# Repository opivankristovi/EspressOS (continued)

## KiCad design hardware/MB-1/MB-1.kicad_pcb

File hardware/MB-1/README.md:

# MB-1: 6 analog in, 2 relays, 2 SSRs (rev A, design)

MB-1 is a 120 × 100 mm carrier board for an ESP32-WROOM-32E module. It is the hardware that the `eos-mb1` board profile in [web/js/boards.js](../../web/js/boards.js) describes. This document is the design: decisions, block diagram, pin map, terminal layout, circuits with values, the KiCad schematic and PCB, a BOM and layout rules.

**Status:** schematic done (generated, netlist-checked). PCB placed and routed (generated; DRC: no errors). Nothing has been ordered or built.

## Design decisions

| Topic | Choice | Why |
|---|---|---|
| Power | 5 V from USB-C only | One connector for power and programming; no supply on the board for 12/24 V. |
| Module | ESP32-WROOM-32E-N4 (PCB antenna) | GPIO 16 and 17 are relay outputs, so a WROVER module is ruled out: on WROVER those pins drive the PSRAM. Use the -32UE (external antenna) if the case sits in a metal cabinet. |
| Outputs | R1, R2: mechanical relays with NO and NC contacts. R3, R4: Omron G3MB-202P solid-state relays | Relays switch AC or DC and have a changeover contact. The SSRs switch AC silently and often (heaters, pumps). |
| Analog in | 6 × 0–10 V | The industrial standard; the same terminals also work as 12–24 V digital inputs. |
| Build | JLCPCB SMD assembly; through-hole parts (terminals, relays, SSRs, fuse holders) soldered by hand | |
| Enclosure | None: a bare board, 120 × 100 mm, five M3 holes | A 6-module DIN case (Camdenboss CNMB/6) has room for only 12 terminal poles per row at 3.5 mm and 9 at 5.08 mm; MB-1 needs 23 and 8. Mount it on standoffs inside a closed cabinet. |

> **Mains warning.** The relay contacts and the SSRs carry mains voltage on this PCB. Wiring and layout have to follow the creepage rules below. The board belongs in a closed enclosure, behind an upstream circuit breaker. Mains work must be done by someone qualified to do it.

## Block diagram

```mermaid
flowchart LR
  USB[USB-C<br/>5 V, data] --> PROT[PTC 1.5 A<br/>TVS 5 V<br/>ESD D+/D-]
  PROT -->|5V| LDO[AP7361C 3.3 V 1 A]
  PROT -->|5V| DRV
  PROT -->|D+/D-| UART[CH340C USB-serial<br/>auto-reset EN/IO0]
  LDO -->|3V3| ESP[ESP32-WROOM-32E]
  UART -->|TX/RX, EN, IO0| ESP
  AIN[AI1-AI6<br/>0-10 V] --> DIV[30k/10k divider<br/>clamp + 100 nF] --> ESP
  ESP -->|GPIO 16-19| DRV[4 × AO3400A low-side<br/>100k gate pull-down]
  DRV --> K12[K1, K2 relay SPDT<br/>COM / NO / NC]
  DRV --> K34[K3, K4 G3MB-202P SSR<br/>+ 2 A fuse]
  ESP <-->|GPIO 23,25,26,27,13,14| IO[IO1-IO6 3.3 V<br/>100 Ω + ESD]
  ESP <-->|GPIO 21/22| I2C[I2C terminals + Qwiic<br/>4.7k pull-ups]
  ESP <-->|GPIO 4| OW[1-Wire terminal<br/>4.7k pull-up]
```

## Pin map (must match the `eos-mb1` profile)

| GPIO | Terminal | Profile uses | Circuit | Notes |
|---|---|---|---|---|
| 36 (SENSOR_VP) | AI1 | ai, di | 0–10 V divider | input only, no internal pull |
| 39 (SENSOR_VN) | AI2 | ai, di | 0–10 V divider | input only |
| 34 | AI3 | ai, di | 0–10 V divider | input only |
| 35 | AI4 | ai, di | 0–10 V divider | input only |
| 32 | AI5 | ai, di | 0–10 V divider | internal pull-up must stay off (`pull: false`) |
| 33 | AI6 | ai, di | 0–10 V divider | same |
| 16 | R1 | do, active high | AO3400A → K1 relay coil | high-Z at reset, so a 100k pull-down keeps it off |
| 17 | R2 | do, active high | AO3400A → K2 relay coil | same |
| 18 | R3 | do, active high | AO3400A → K3 SSR input | same |
| 19 | R4 | do, active high | AO3400A → K4 SSR input | same |
| 23 | IO1 | di, do, pwm | 100 Ω + ESD | 3.3 V logic |
| 25 | IO2 | di, do, pwm | 100 Ω + ESD | |
| 26 | IO3 | di, do, pwm | 100 Ω + ESD | |
| 27 | IO4 | di, do, pwm | 100 Ω + ESD | |
| 13 | IO5 | di, do, pwm | 100 Ω + ESD | |
| 14 | IO6 | di | 100 Ω + ESD | input only in the profile: GPIO 14 outputs PWM during boot |
| 21 | SDA | I2C bus | 4.7k to 3V3, ESD | terminal and Qwiic connector |
| 22 | SCL | I2C bus | 4.7k to 3V3, ESD | |
| 4 | DQ | 1-Wire | 4.7k to 3V3, ESD | DS18B20 |
| 0 | — | BOOT button, auto-reset | 10k pull-up | strapping pin, not a terminal |
| EN | — | RESET button, auto-reset | 10k + 1 µF | |
| 1 / 3 | — | U0TXD / U0RXD → CH340C | | serial console and flashing |
| 2, 5, 12, 15 | — | not connected | | strapping pins; leave them open |
| 6–11 | — | module flash | | never route |

## Terminals

Mains is on the lower edge (5.08 mm pitch, rated 250 V). Safety extra-low voltage (SELV) is on the upper edge (3.5 mm pitch). USB-C and the RESET and BOOT buttons are on the left edge.

**Upper edge (SELV), left to right**

| Block | Positions |
|---|---|
| I2C (4) | 3V3 · SDA · SCL · GND |
| 1-Wire (3) | 3V3 · DQ · GND |
| Analog (8) | AI1 · AI2 · AI3 · AI4 · AI5 · AI6 · GND · GND |
| GPIO (8) | IO1 · IO2 · IO3 · IO4 · IO5 · IO6 · 3V3 · GND |
| Qwiic | Qwiic/STEMMA QT socket, at the right end |

**Lower edge (mains), left to right**

| Block | Positions | Rating on this board |
|---|---|---|
| R1 (3) | COM · NO · NC | 250 V AC / 30 V DC, 5 A (derated from the relay's 10 A for PCB and terminals) |
| R2 (3) | COM · NO · NC | same |
| R3, R4 (3) | SSR L in · R3 Load · R4 Load | 100–240 V AC, 0.1–2 A each, AC only; a 2 A fuse per SSR on board |

The two SSRs share one L input (J4 pin 1); each has its own fuse after that terminal. Wire both loads from the same phase.

The 3V3 terminal positions share a 200 mA PTC, so a shorted sensor cable cannot reset the ESP32.

## Circuits

### Power: USB-C 5 V
- J1: USB-C receptacle (USB 2.0, 16-pin). CC1 and CC2 each go to GND through their own 5.1 kΩ (R1, R2). Without those the C-to-C charger gives no power.
- F1: PTC, 1.5 A hold, on VBUS. D1: SMAJ5.0A TVS from VBUS to GND. C1 100 µF/16 V and C2 10 µF on the 5V rail.
- U2: AP7361C-33E (1 A, about 0.36 V dropout) from 5V to 3V3. Input C3 10 µF, output C4 22 µF + C5 100 nF. Do not use AMS1117: its 1.1 V dropout leaves no margin when USB VBUS sags.
- D2 + R3 1 kΩ: green power LED on 3V3.
- **Budget:** ESP32 Wi-Fi peaks at about 500 mA; each relay coil draws about 72 mA; each SSR input about 10–20 mA; LEDs about 10 mA. The total peak is about 0.75 A. Use a USB-C charger or a USB 3 port rated for at least 1 A. A USB 2 port (500 mA) may brown out when Wi-Fi transmits with both relays on.

### USB-serial and auto-reset
- U3: CH340C (internal oscillator), powered from **3V3**: VCC and V3 tied to 3V3, C6 100 nF. At 3.3 V its TXD cannot over-drive the ESP32's RX pin, which is not 5 V tolerant.
- U4: USBLC6-2SC6 on D+/D− at the connector.
- U3 TXD → ESP32 RXD0 (GPIO 3); U3 RXD → ESP32 TXD0 (GPIO 1).
- Auto-reset is the classic two-transistor circuit (Q1, Q2 MMBT3904, R4/R5 10 kΩ bases):
  - DTR → R4 → Q1 base. Q1 emitter goes to RTS and its collector to IO0.
  - RTS → R5 → Q2 base. Q2 emitter goes to DTR and its collector to EN.
- EN: R6 10 kΩ to 3V3 and C7 1 µF to GND (Espressif's RC delay); SW1 RESET to GND.
- IO0: R7 10 kΩ to 3V3; SW2 BOOT to GND. **Both buttons must be reachable through the front of the case:** the node firmware (mesh) uses BOOT at power-up to reopen its setup network.

### ESP32 module
- U1: ESP32-WROOM-32E-N4. 3V3 decoupling at the module: C8 22 µF + C9 100 nF + C10 100 nF.
- The antenna sits at a board edge with no copper on any layer under or next to it (see Espressif's keep-out drawing), as far as possible from the relays and the mains area.

### Outputs R1–R4 (×4, n = 1…4)
Each output is a low-side N-MOSFET with its gate held low, so the output is off while the ESP32 boots (GPIO 16–19 float at reset).

- GPIO → Rg(n) 100 Ω → gate Qn (AO3400A). Rpd(n) 100 kΩ from gate to GND.
- **R1, R2 (relays K1, K2, Omron G2RL-1 DC5):** coil between 5V and the drain. Flyback diode D(n) 1N4148W across the coil (cathode to 5V). Indicator LED + 1 kΩ from 5V to the drain.
- **R3, R4 (SSRs K3, K4, G3MB-202P):** input + to 5V, input − to the drain. Indicator LED + 1 kΩ from 5V to the drain. Load side: terminal "SSR L in" (shared) → fuse F3/F4 (2 A time-lag, TR5) → SSR terminal; the other SSR terminal goes to terminal "R3 Load" / "R4 Load". Pin order from the Omron data sheet: 1 and 2 load, 3 input +, 4 input −.
- G3MB-202P notes for the user:
  - It switches AC only; it never turns a DC load off.
  - Its built-in snubber passes a small leakage current, so a very small load such as an LED lamp under about 0.1 A can glow while the output is off. The profile note says 0.1–2 A for that reason.

### Analog inputs AI1–AI6 (×6)
Terminal → Rs 30 kΩ 1 % → node → ESP32 pin; node → Rb 10 kΩ 1 % to GND; node → C 100 nF to GND; node → BAT54S common pin. BAT54S pin 1 goes to GND and pin 2 to 3V3.

- Divider ratio 4: **10 V at the terminal = 2.5 V at the ADC**, inside the ESP32's useful 12 dB range. Full scale is reached at about 13 V.
- Input impedance is 40 kΩ, as 0–10 V sensors expect.
- Protected up to 30 V continuous: the clamp current is (30 − 3.6) / 30k ≈ 0.9 mA per input, well below what the ESP32 draws from 3V3.
- **As digital inputs** (`di`): high above about 10 V and low below about 3.3 V at the terminal. That works for 12 V and 24 V signals, but not for 5 V logic: use an IO terminal for that.
- **Scaling in the editor:** the AI block maps raw 0…4095 to min…max, and "Value at 3.3 V" is 13.2 V at the terminal. For a 0–10 V sensor that should read 0–100 %, set min 0 and max 132. The ESP32 ADC is not linear near both ends, so expect ±2–3 % without calibration (see Follow-ups).

### GPIO IO1–IO6 (×6)
- GPIO ← 100 Ω → terminal; ESD: U5 TPD4E05U06 (IO1–IO4), U6 TPD4E05U06 (IO5, IO6, SDA, SCL).
- These are 3.3 V logic pins, without isolation or level shifting. Inputs must stay within 0–3.3 V. Outputs give at most about 12 mA, enough for an LED, an external relay module input or a MOSFET module.

### I2C and 1-Wire
- SDA (GPIO 21) and SCL (GPIO 22): R 4.7 kΩ each to 3V3. Wired to the I2C terminal and J5 (JST SM04B-SRSS-TB, Qwiic pinout GND · 3V3 · SDA · SCL).
- DQ (GPIO 4): R 4.7 kΩ to 3V3. ESD: D (PESD3V3L1BA).
- F2: PTC 200 mA hold between 3V3 and the "3V3 out" net that feeds every 3V3 terminal position and J5.

## Schematic

[MB-1.kicad_sch](MB-1.kicad_sch) is the schematic (KiCad 8 format; it opens in KiCad 8, 9 and 10), and [MB-1.pdf](MB-1.pdf) is a print of it. Open [MB-1.kicad_pro](MB-1.kicad_pro) in KiCad.

**It is generated.** [gen_schematic.py](gen_schematic.py) holds every part, its value, footprint and part number, and the net on each pin. The script copies the symbols from KiCad's own libraries and draws the sheet:
- six blocks, matching the sections above;
- net labels at the pins and power symbols for GND, +5V and +3V3;
- a no-connect flag on every pin that isn't used.

To change the circuit, edit the script and generate again, rather than editing the sheet by hand:

```bash
python gen_schematic.py
kicad-cli sch erc MB-1.kicad_sch
kicad-cli sch export netlist --format kicadsexpr -o MB-1.net MB-1.kicad_sch
python check_netlist.py MB-1.net
kicad-cli sch export pdf -o MB-1.pdf MB-1.kicad_sch
```

[check_netlist.py](check_netlist.py) compares the netlist KiCad reads from the sheet with the nets in the script, pin by pin. A label that lands on the wrong pin would short or split a net without any ERC error. The current sheet gives 72 nets and 0 differences.

**ERC:** the electrical check has one expected error: "power output connected to power output" between U2 VO and U3 V3. The CH340C datasheet ties V3 to VCC when the chip runs at 3.3 V. Exclude it in KiCad's ERC dialog. On a KiCad install whose library tables were never set up, `kicad-cli` also lists "library not in the current configuration" warnings; those go away once KiCad has been started once.

**Parts that needed care:**
- *K3/K4 symbol:* KiCad has no Omron G3MB. The sheet uses the Sharp S202S02 symbol, which does the same job: input 3 (+) and 4 (−), output 1 and 2.
- *K3/K4 footprint:* `MB-1:Omron_G3MB-202P_SIP4` lives in the project library [MB-1.pretty](MB-1.pretty), drawn from Omron's G3MB data sheet (Cat. No. GC RLY8, page 3). It has four 1.0 mm holes on 1.8 mm pads, at 0, 7.62, 17.78 and 20.32 mm from pin 1 (top view). Pins 1 and 2 are the load and 3 (+) and 4 (−) the input. The body is 24.5 × 5.5 mm, with pin 4 1.69 mm from the body end. The [fp-lib-table](fp-lib-table) next to the project points KiCad to it. This is the standard G3MB-202P only: the "-4" variant has a different hole layout.
- *F3/F4:* these use TR5 fuse sockets (Littelfuse 560/460 series), so a blown fuse can be swapped.
- *K1/K2:* Omron G2RL-1 rather than the common HF3FF/SRD cube: on the cube footprint COM sits 6.3 mm from a coil pin, which leaves no room for 6 mm creepage after pads. The G2RL has its coil and contacts at opposite ends (KiCad footprint `Relay_THT:Relay_SPDT_Omron_G2RL-1`).

Reference designators on the sheet:

| Function | Refs |
|---|---|
| Power | J1, R1–R3, F1, D1, C1–C5, LED1, U2 |
| USB-serial, reset | U3, U4, Q1, Q2, R4–R7, C6, C7, SW1 (RESET), SW2 (BOOT) |
| ESP32 | U1, C8–C10 |
| Outputs (n = 1…4) | gate resistor R11–R14, gate pull-down R15–R18, MOSFET Q3–Q6, LED2–LED5 with R19–R22, relays K1/K2 with flyback D4/D5, SSRs K3/K4 with fuses F3/F4, terminals J2–J4 |
| Analog in (n = 1…6) | series R23–R28 (30k), to GND R29–R34 (10k), C11–C16, clamp D6–D11, terminal J6 |
| GPIO, buses | series R35–R40, ESD U5/U6 and D3, I2C pull-ups R8/R9, 1-Wire pull-up R10, PTC F2, terminals J7–J9, Qwiic J5 |

## PCB

[MB-1.kicad\_pcb](MB-1.kicad_pcb): two layers, 120 × 100 mm, all parts on top. Renders: [top](MB-1-top.png), [bottom](MB-1-bottom.png). Like the schematic it is generated, and then routed by a script:

```bash
"%LOCALAPPDATA%\Programs\KiCad\10.0\bin\python.exe" gen_pcb.py
"%LOCALAPPDATA%\Programs\KiCad\10.0\bin\python.exe" route.py
kicad-cli pcb drc MB-1.kicad_pcb
```

* **[gen\_pcb.py](gen_pcb.py)** reads the parts and nets from `gen_schematic.py`, places every footprint, and writes the outline, mounting holes, silkscreen labels, ground pours and design rules. Footprints keep their schematic links, so *Update PCB from Schematic* in KiCad still works. Ground pads that tracks would fence in (U4, U5, U6, the AI filter caps, each output driver's MOSFET source and gate pull-down) get a locked via before routing. Strips 0.5 mm wide along the board edge keep tracks off it. `gen_pcb.py --silk` copies the part fields (values, MPN, LCSC) from `gen_schematic.py` and redoes the silkscreen on the routed board, without touching copper.
* **[route.py](route.py)** exports the board to Freerouting, routes it (about 15 minutes), reads the result back and cleans up after it: it removes loose vias and dead-end stubs, fills the pours, adds ground stitching vias on a 4 mm grid (0.5 mm from any other hole), joins every piece of ground pour that is cut off from the main ground with a via, and widens the few tracks Freerouting necks below 0.13 mm. Freerouting's router is deterministic and can stall with a net open; route.py then retries with a slightly larger clearance margin. It needs the Freerouting 2.5 jar (from its GitHub releases) and Java 25; the native `freerouting-cli` 2.5.0 build crashes and then hangs. Freerouting's log goes to `MB-1.route.log`.

**Layout.** SELV parts fill the top 65 mm: terminals along the top edge, the ESP32 at the right edge with its antenna past the copper, USB-C and the power and USB-serial parts on the left, the four output drivers in a row above the keep-out. A 6 mm keep-out band across the board (y 65.6–71.6 mm) carries no copper on either layer. Below it are only mains parts: K1/K2 above J2/J3 on the left, K3/K4 with F3/F4 and J4 on the right. Relay coils and SSR inputs are the only things that bridge the band, through the parts themselves.

**Rules** ([MB-1.kicad\_dru](MB-1.kicad_dru) and the net classes in the project):

|Net class / rule|Clearance|Track|
|-|-|-|
|Default|0.2 mm|0.25 mm|
|Power (GND, +5V, +3V3, VBUS, 3V3 out, relay drivers)|0.2 mm|0.6 mm|
|Mains (relay contacts, SSR load side)|2.0 mm|2.0 mm|
|Mains to anything not mains|6.0 mm| |
|Mains to a mounting hole|6.0 mm| |

Mains tracks are 2 mm wide on both layers. That carries 5 A with about 20 °C rise on 1 oz copper; order 2 oz copper, or tin the mains tracks, if the relays will switch close to 5 A continuously.

**DRC:** no errors and no unconnected items. The warnings left are "footprint library not in the current configuration" (as with ERC, until KiCad has been started once) and 8 places in the driver row where reference text touches a pad; the fab clips silkscreen off pads.

**Open before ordering:**

* Milled slots between relay coil and contact pins, and between SSR input and load pins (the layout rules ask for them; the 6 mm clearance already holds without them).
* Gerbers, and a check of the part rotations in JLCPCB's placement preview (see *Ordering at JLCPCB*).
* A look at the board in KiCad's 3D viewer and a printout at 1:1 to check the terminal and relay footprints against real parts.

## 3D model for an enclosure

[3d/MB-1.stl](3d/MB-1.stl) is the assembled board as one mesh (binary STL, mm), for designing an enclosure in Fusion, TinkerCAD or any CAD that imports STL. [make\_3d.py](make_3d.py) makes it from the routed board:

```bash
"%LOCALAPPDATA%\Programs\KiCad\10.0\bin\python.exe" make_3d.py
```

KiCad's library has no 3D model for the USB-C socket, the G2RL relays, the 1812 PTC or the project's own G3MB footprint. For those the script adds a solid block: the body outline from the footprint's fabrication drawing, the height from the data sheet (maximum).

**Coordinates.** The origin is the board's lower-left corner, with low voltage at the top and mains at the bottom, as in the renders. X runs along the 120 mm edge and Y along the 100 mm edge. Z runs up from the bottom of the board, so the top surface is at z = 1.6.

**What the enclosure has to clear** (from the model):

|Item|Where (mm)|Height (z, mm)|
|-|-|-|
|Board|0–120 × 0–100, 1.6 thick, 2 mm corner radius|0–1.6|
|Mounting holes, M3 (3.2 mm)|(3.5, 3.5), (116.5, 3.5), (62, 3.5), (3.5, 96.5), (116.5, 96.5)| |
|Pins and solder below the board|whole board|down to −2.9: standoffs of 5 mm or more|
|SSRs K3/K4 (tallest)|x 64.2–69.8 and 72.2–77.8, y 15.5–40.1|up to 22.1|
|Relays K1/K2|x 9.5–22.0 and 28.4–41.1, y 13.4–42.3|up to 17.3|
|Mains terminals J2, J3, J4 (screws on top, wires in from the bottom edge)|y 0.9–10.7; x 8.7–43.7 and 80.7–94.9|up to 15.4|
|Low-voltage terminals J6–J9 (screws on top, wires in from the top edge)|y 85.8–99.0, x 10.1–99.6|up to 10.8|
|Qwiic socket J5 (opening to the top edge)|x 98–104, y 93.5–98.5|up to 4.6|
|USB-C J1 (opening to the left edge)|mouth at x 0.7, y 65.5–74.5|1.6–4.9|
|RESET / BOOT buttons (pressed from above)|x 1.8–8.2, y 44.9–58.6|up to 3.1|
|Fuse sockets F3/F4|x 99–108, y 9–29|socket 7.2; the TR5 fuse sits on top: measure with the fuse fitted|
|ESP32 antenna|x 94.5–119.5, y 55–73 (module), antenna at the right edge|keep metal away from the right edge|

The enclosure has to keep fingers off the mains side. All mains copper (relay contacts, SSR load pins, fuses, terminals J2–J4) lies below the copper-free band at y 28.4–34.4; the relay and SSR bodies straddle that band.

## BOM (one board)

Every part has an LCSC number (the `LCSC` field in the schematic and PCB, set in the `ORDER` table of [gen\_schematic.py](gen_schematic.py)). They were looked up in JLCPCB's parts catalogue on 12 November 2026; stock changes, so check the numbers again when ordering. **Basic** parts carry no setup fee at JLCPCB; every other (extended) SMD part costs $3 per order. MB-1 has 15 extended SMD parts.

**SMD, placed by JLCPCB**

| Ref | Qty | Part | MPN | LCSC | Type |
|---|---|---|---|---|---|
| U1 | 1 | ESP32 module, 4 MB | Espressif ESP32-WROOM-32E-N4 | C701341 | extended |
| U2 | 1 | LDO 3.3 V 1 A, SOT-223 | Diodes AP7361C-33E-13 | C500795 | extended (low stock, about 2,500) |
| U3 | 1 | USB-serial, SOP-16 | WCH CH340C | C84681 | extended |
| U4 | 1 | USB ESD, SOT-23-6 | ST USBLC6-2SC6 | C7519 | extended |
| U5, U6 | 2 | 4-ch ESD, USON-10 | TI TPD4E05U06DQAR | C138714 | extended |
| Q1, Q2 | 2 | NPN, SOT-23 | MMBT3904 | C20526 | basic |
| Q3–Q6 | 4 | N-MOSFET logic level, SOT-23 | AOS AO3400A | C20917 | basic |
| D1 | 1 | TVS 5 V, SMA | Littelfuse SMAJ5.0A | C83329 | extended |
| D3 | 1 | ESD diode for DQ, SOD-323 | Nexperia PESD3V3L1BA,115 | C51450 | extended |
| D4, D5 | 2 | Flyback diode, SOD-123 | 1N4148W | C81598 | basic |
| D6–D11 | 6 | Schottky pair, SOT-23 | Nexperia BAT54S,215 | C47546 | extended |
| F1 | 1 | PTC 1.5 A hold, 1812 | Bourns MF-MSMF150-2 | C89648 | extended |
| F2 | 1 | PTC 0.2 A hold, 1206 | Bourns MF-NSMF020-2 | C185112 | extended |
| J1 | 1 | USB-C 16-pin receptacle | HRO TYPE-C-31-M-12 | C165948 | extended |
| J5 | 1 | Qwiic socket | JST SM04B-SRSS-TB(LF)(SN) | C160404 | extended |
| SW1, SW2 | 2 | Tact switch 5.2 mm | E-Switch TL3342F450QG | C2886897 | extended (about 600 in stock) |
| LED1 | 1 | LED green 0603 | KENTO KT-0603G | C12624 | extended |
| LED2–LED5 | 4 | LED red 0603 | KENTO KT-0603R | C2286 | basic |
| C1 | 1 | 100 µF 16 V electrolytic, 6.3 × 5.4 mm | KNSCHA RVT100UF16V67RV0016 | C2887276 | extended |
| C2, C3 | 2 | 10 µF 25 V X5R 0805 | Samsung CL21A106KAYNNNE | C15850 | basic |
| C4, C8 | 2 | 22 µF 25 V X5R 0805 | Samsung CL21A226MAQNNNE | C45783 | basic |
| C5, C6, C9–C16 | 10 | 100 nF 50 V X7R 0603 | Yageo CC0603KRX7R9BB104 | C14663 | basic |
| C7 | 1 | 1 µF 50 V X5R 0603 | Samsung CL10A105KB8NNNC | C15849 | basic |
| R1, R2 | 2 | 5.1 kΩ 1 % 0603 | Uniroyal 0603WAF5101T5E | C23186 | basic |
| R3, R19–R22 | 5 | 1 kΩ 1 % 0603 | Uniroyal 0603WAF1001T5E | C21190 | basic |
| R4–R7, R29–R34 | 10 | 10 kΩ 1 % 0603 | Uniroyal 0603WAF1002T5E | C25804 | basic |
| R8–R10 | 3 | 4.7 kΩ 1 % 0603 | Uniroyal 0603WAF4701T5E | C23162 | basic |
| R11–R14, R35–R40 | 10 | 100 Ω 1 % 0603 | Uniroyal 0603WAF1000T5E | C22775 | basic |
| R15–R18 | 4 | 100 kΩ 1 % 0603 | Uniroyal 0603WAF1003T5E | C25803 | basic |
| R23–R28 | 6 | 30 kΩ 1 % 0603 | Uniroyal 0603WAF3002T5E | C22984 | basic |

Notes:

* *C1* is 5.4 mm tall rather than 7.7 mm: no 100 µF part in the 6.3 × 7.7 mm size was in stock. Its pads are 0.1 mm further in than the board's 6.3 × 7.7 mm land pattern, which takes it without change.
* *F2* is the 1206 version (MF-**N**SMF020-2). The MSMF series that the first BOM named is 1812 and would not fit the footprint.

**Through-hole, soldered by hand** (order from LCSC or any distributor)

| Ref | Qty | Part | MPN | LCSC | Stock at LCSC |
|---|---|---|---|---|---|
| K1, K2 | 2 | Relay SPDT 5 V 12 A | Omron G2RL-1 DC5 | C1524672 | about 1,100 |
| K3, K4 | 2 | SSR 2 A AC, zero-cross, SIP-4 | Omron G3MB-202P DC5 | C19591980 | **none**: buy elsewhere (Mouser, DigiKey, Farnell) |
| F3, F4 | 2 | TR5 fuse socket | Littelfuse 56000001009 | C142909 | yes |
| (in F3, F4) | 2 | Fuse 2 A time-lag, TR5 | Littelfuse 37212000001 | C142854 | about 1,400 |
| J2–J4 | 3 | Screw terminal 3-pos 5.08 mm | Phoenix MKDS 1,5/ 3-5,08 (1715734) | C480520 | about 1,100 |
| J6, J7 | 2 | Screw terminal 8-pos 3.5 mm | Phoenix PT 1,5/ 8-3,5-H (1984675) | C5484501 | **none**: buy elsewhere |
| J8 | 1 | Screw terminal 3-pos 3.5 mm | Phoenix PT 1,5/ 3-3,5-H (1984620) | C3816291 | about 500 |
| J9 | 1 | Screw terminal 4-pos 3.5 mm | Phoenix PT 1,5/ 4-3,5-H (1984633) | C5144867 | about 200 |
| — | 5 | M3 standoffs and screws | any | | |

### Ordering at JLCPCB

```bash
"%LOCALAPPDATA%\Programs\KiCad\10.0\bin\python.exe" jlc.py
"%LOCALAPPDATA%\Programs\KiCad\10.0\bin\python.exe" jlc_check.py
```

[jlc.py](jlc.py) writes the three files JLCPCB asks for, from the routed board:

* [jlcpcb/MB-1-gerbers.zip](jlcpcb/MB-1-gerbers.zip): copper, mask, paste and silkscreen on both sides, the outline, and plated and non-plated drill files (Protel file names, silkscreen clipped at the mask openings, drill in mm), as JLCPCB's KiCad guide asks. Two-layer board, 120 × 100 mm.
* [jlcpcb/MB-1-bom.csv](jlcpcb/MB-1-bom.csv): the 89 SMD parts in 32 lines, with their LCSC numbers.
* [jlcpcb/MB-1-cpl.csv](jlcpcb/MB-1-cpl.csv): position (mm from the board's lower-left corner) and rotation of each SMD part.

JLCPCB places its own library footprint for each LCSC part, and for some packages its zero rotation or origin differs from KiCad's. The `JLC_FIX` table in jlc.py corrects those: +180° for the SOT-23 parts (Q1–Q6, D6–D11) and the AP7361C, +270° for the CH340C, USBLC6 and TPD4E05U06, and +270° plus a 3.68 mm offset for the ESP32. The USB-C socket keeps its rotation but gets a 1.57 mm offset. [jlc_check.py](jlc_check.py) verifies the result the way JLCPCB's placement preview does: it fetches each part's footprint from EasyEDA (JLCPCB's library) and fits its numbered pads onto the KiCad pads. It also compares both libraries' pin names per pad, which caught the red LEDs (C2286): their pad 1 is the anode, KiCad's is the cathode, so a plain pad-number match would have turned them round. All 89 parts check out: right rotation, centred within 0.1 mm, and the same pinout and polarity. The largest pad difference left is 0.4 mm on the CH340C, where JLCPCB's SOIC land pattern is wider.

Still worth one look in JLCPCB's own placement preview when ordering (it needs a JLCPCB account): the check uses the same library data, but the preview is what the factory goes by.

## Layout rules

- **Mains area** (K1–K4 load side, F3/F4, J2–J4) on the lower part of the board.
  - At least **6 mm creepage and clearance** between any mains net and any SELV net.
  - Milled slots under the relays and SSRs between coil/input pins and contact/load pins.
  - At least 3 mm between different mains channels.
  - Load traces at least 3 mm wide on 1 oz copper, or 2 mm on 2 oz, both layers, for 5 A.
  - No ground pour inside the mains area.
- **SELV area:** one solid GND plane. The ESP32, the LDO and the CH340C sit away from the relay coil current loops.
- Antenna keep-out at the right board edge, away from the relays; keep the cabinet wall near that edge non-metallic.
- Each analog divider sits close to its ESP32 pin, with the 100 nF capacitor right at the pin.
- Silkscreen: terminal labels exactly as the profile names them (AI1…AI6, R1…R4, IO1…IO6), plus "MB-1 rev A".

## Bring-up checklist

1. With no module fitted: power on USB-C and check 5V and 3V3. Measure that DRV1–4 are high (outputs off).
2. Fit the module and flash `pio run -t upload && pio run -t uploadfs` over USB with no button presses. That tests the auto-reset circuit.
3. In the editor, choose Settings → Board → **MB-1** and let it restart. Deploy a program with one DO per output and check that each relay and SSR clicks or switches on its own channel. Power-cycle and confirm that nothing switches during boot.
4. Feed 0, 5 and 10 V to each AI and check the readings (expect raw about 0, 1550 and 3100).
5. Scan I2C with a sensor on the Qwiic socket, and read a DS18B20 on the 1-Wire terminal.

## Follow-ups (not part of rev A)

- **Analog in volts.** Let the firmware read the ADC with `analogReadMilliVolts` (Espressif's calibration), and give a profile terminal an optional scale (here ×4). The AI block would then show terminal volts, so users wouldn't need the "max 132" rule above. That needs a profile schema change in both validators.
- **Power option.** A 24 V version (buck converter to 5 V) for cabinets where USB power is unusual.

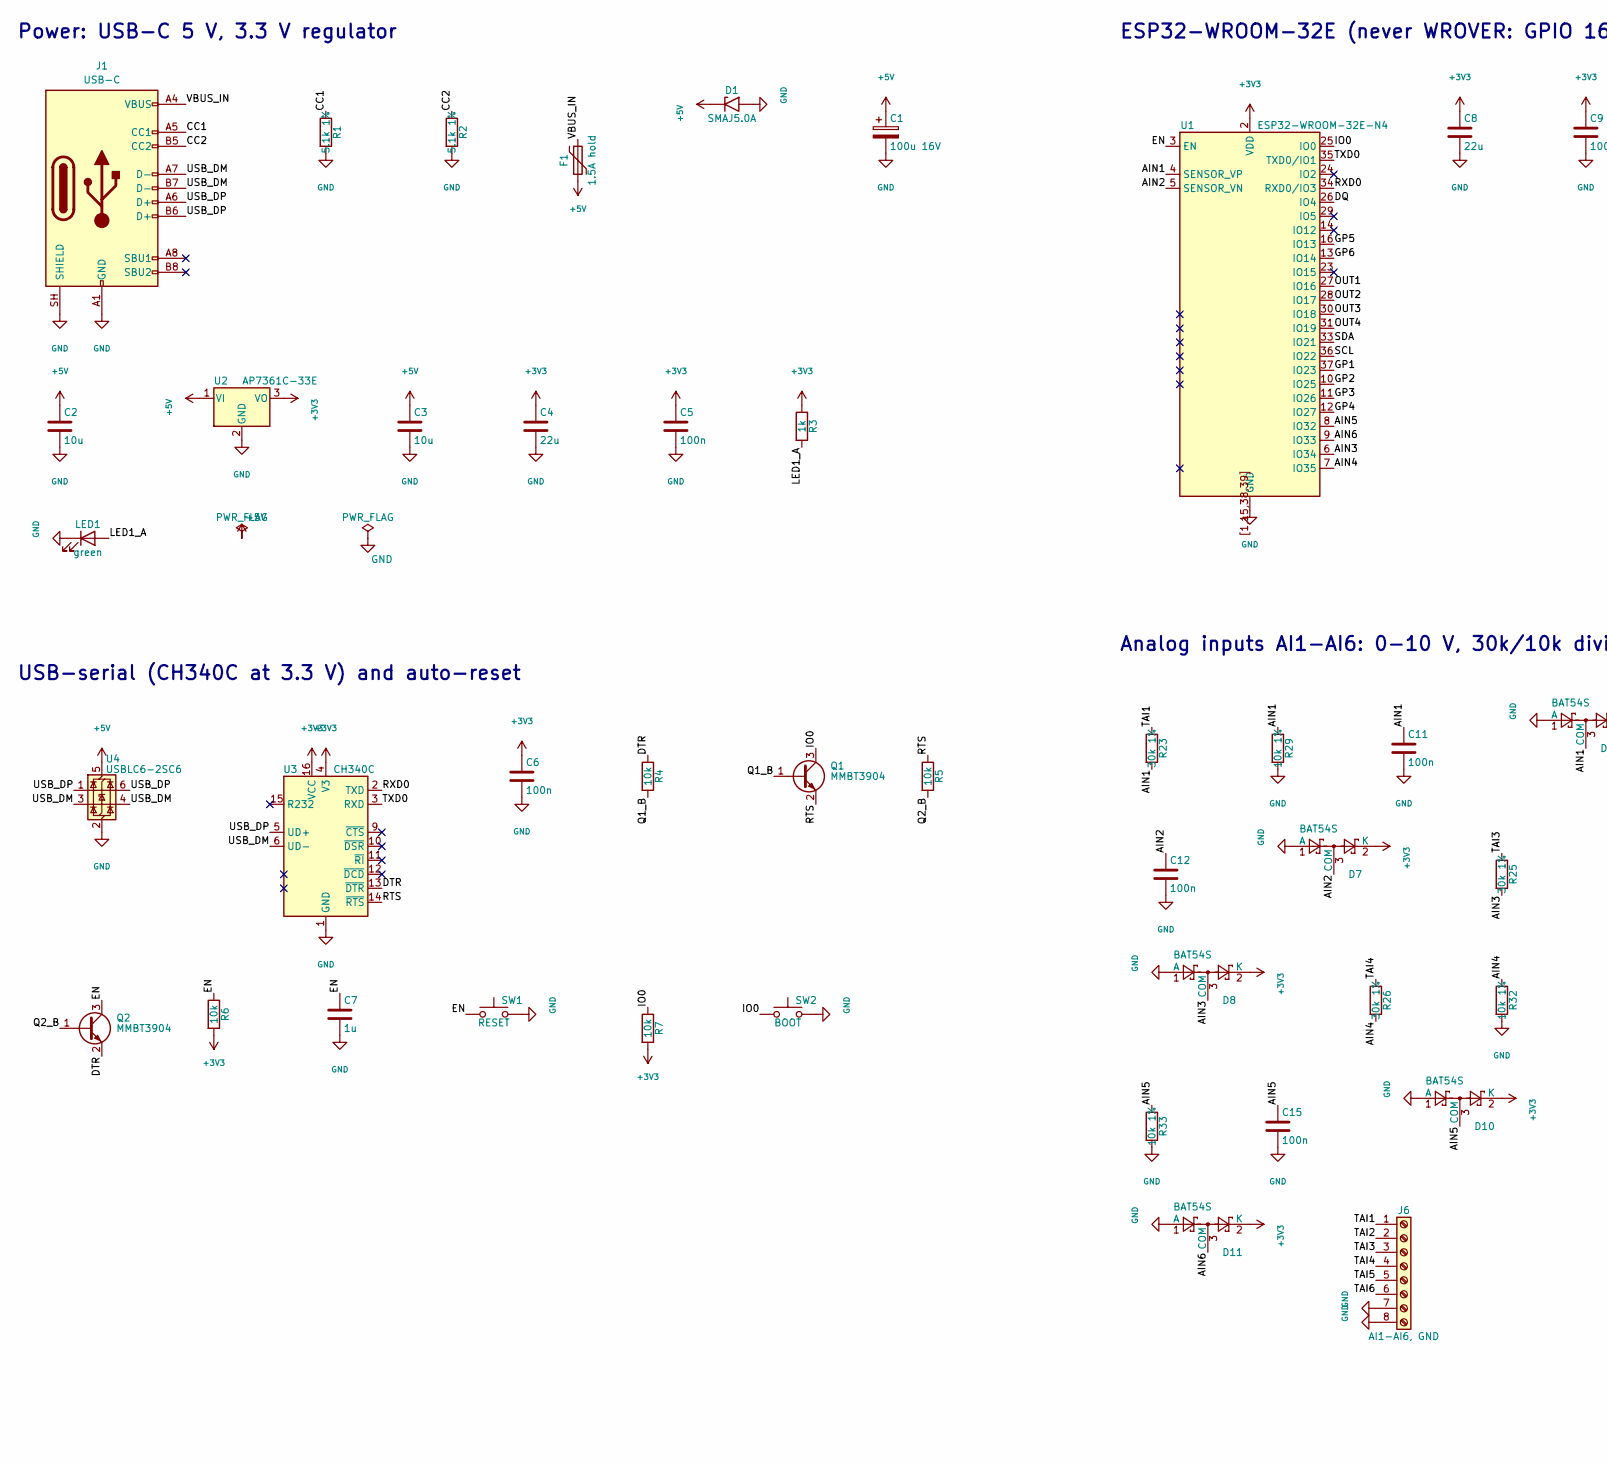
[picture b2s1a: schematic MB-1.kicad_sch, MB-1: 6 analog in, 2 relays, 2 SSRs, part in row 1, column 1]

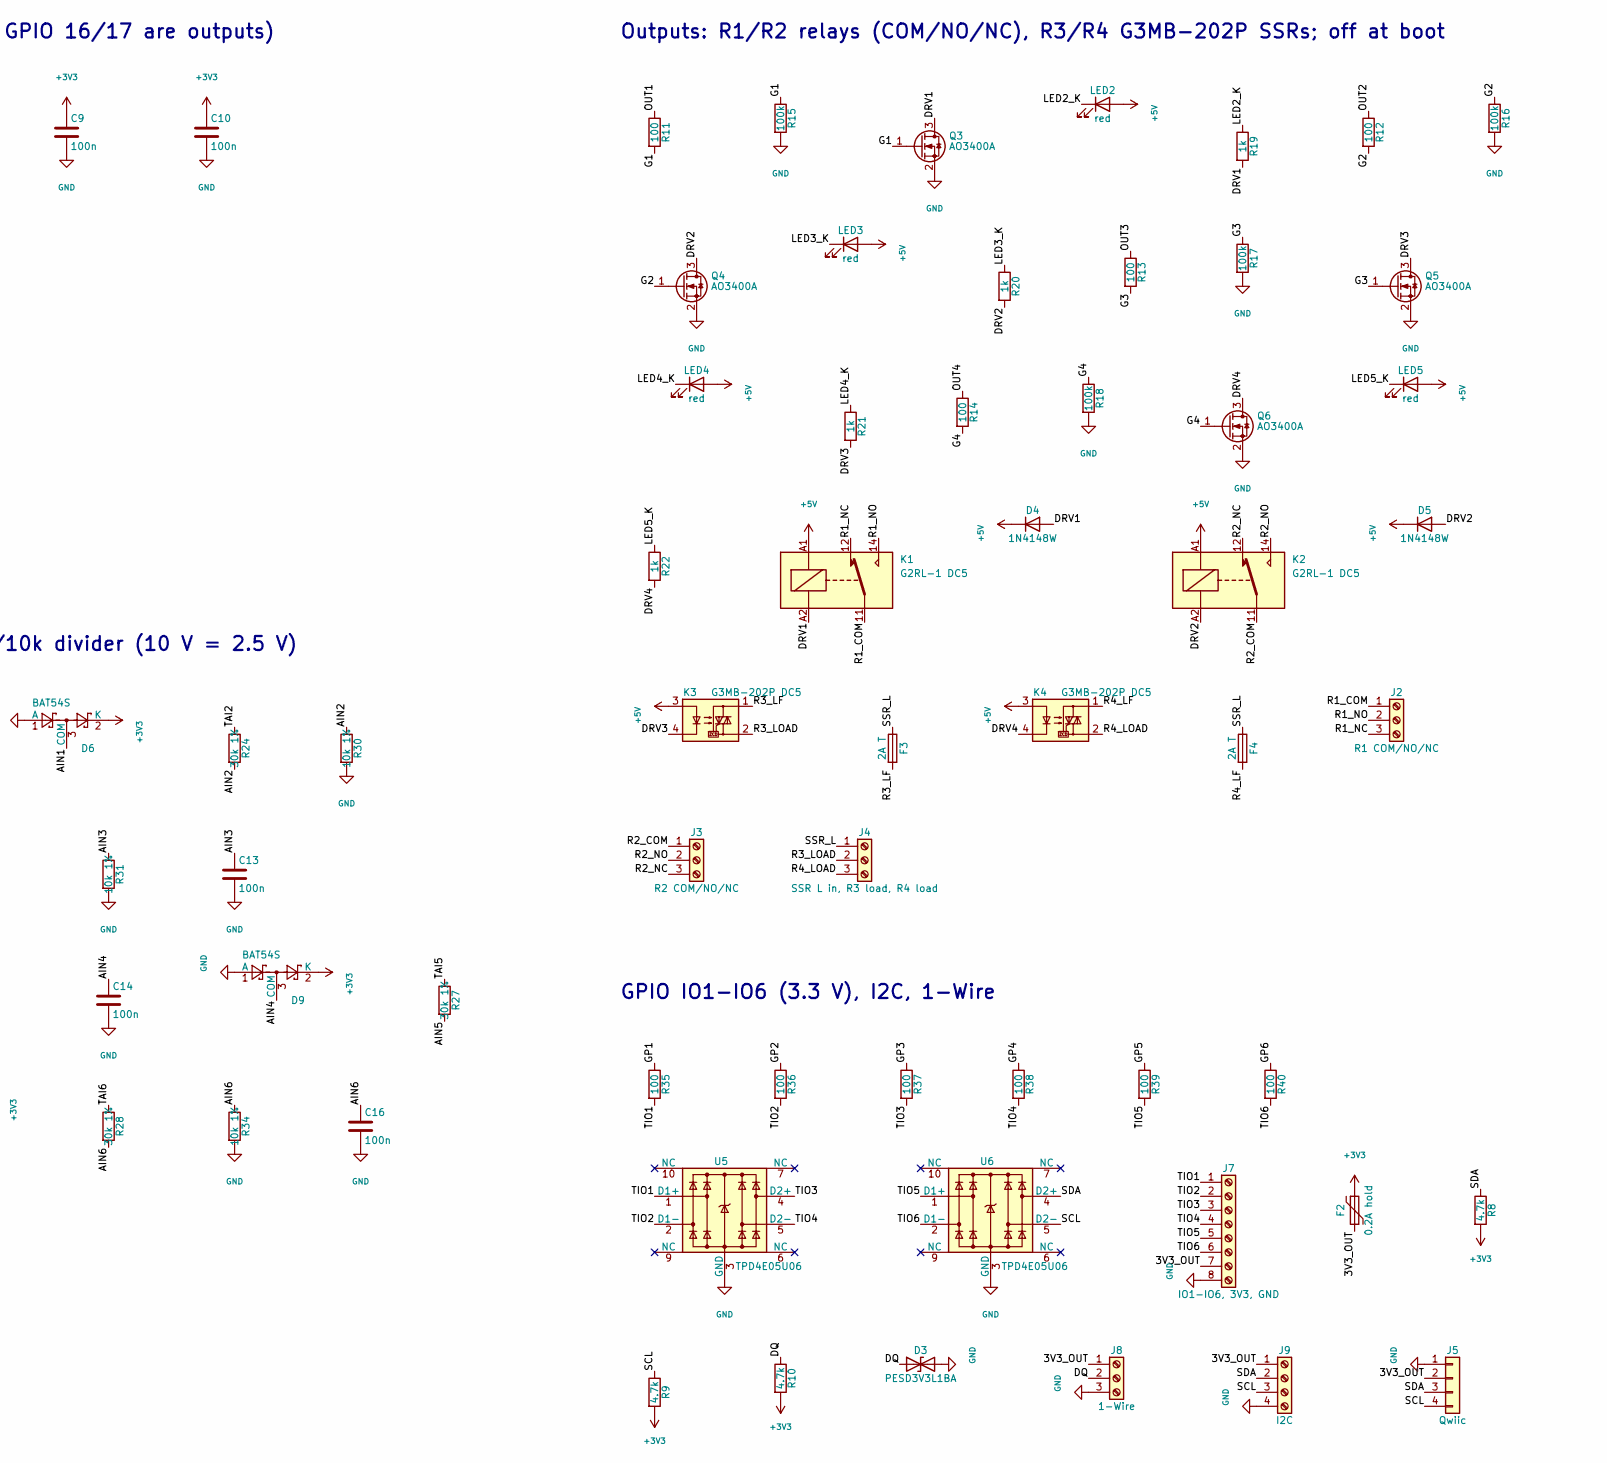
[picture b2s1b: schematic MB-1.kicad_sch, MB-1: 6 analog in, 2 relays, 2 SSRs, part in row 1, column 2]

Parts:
C1: 100u 16V; CP_Elec_6.3x7.7; MPN KNSCHA RVT100UF16V67RV0016; LCSC C2887276
C2, C3: 10u; C_0805_2012Metric; MPN Samsung CL21A106KAYNNNE; LCSC C15850
C4, C8: 22u; C_0805_2012Metric; MPN Samsung CL21A226MAQNNNE; LCSC C45783
C5, C6, C9, C10, C11, C12, C13, C14, C15, C16: 100n; C_0603_1608Metric; MPN Yageo CC0603KRX7R9BB104; LCSC C14663
C7: 1u; C_0603_1608Metric; MPN Samsung CL10A105KB8NNNC; LCSC C15849
D1: SMAJ5.0A; D_SMA; MPN Littelfuse SMAJ5.0A; LCSC C83329
D3: PESD3V3L1BA; D_SOD-323; MPN Nexperia PESD3V3L1BA,115; LCSC C51450
D4, D5: 1N4148W; D_SOD-123; MPN 1N4148W; LCSC C81598
D6, D7, D8, D9, D10, D11: BAT54S; SOT-23; MPN Nexperia BAT54S,215; LCSC C47546
F1: 1.5A hold; Fuse_1812_4532Metric; MPN Bourns MF-MSMF150-2; LCSC C89648
F2: 0.2A hold; Fuse_1206_3216Metric; MPN Bourns MF-NSMF020-2; LCSC C185112
F3, F4: 2A T; Fuseholder_TR5_Littelfuse_No560_No460; MPN Littelfuse 56000001009; LCSC C142909
J1: USB-C; USB_C_Receptacle_HRO_TYPE-C-31-M-12; MPN HRO TYPE-C-31-M-12; LCSC C165948
J2: R1 COM/NO/NC; TerminalBlock_Phoenix_MKDS-1,5-3-5.08_1x03_P5.08mm_Horizont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; MPN Phoenix MKDS 1,5/ 3-5,08 (1715734); LCSC C480520
J3: R2 COM/NO/NC; TerminalBlock_Phoenix_MKDS-1,5-3-5.08_1x03_P5.08mm_Horizont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; MPN Phoenix MKDS 1,5/ 3-5,08 (1715734); LCSC C480520
J4: SSR L in, R3 load, R4 load; TerminalBlock_Phoenix_MKDS-1,5-3-5.08_1x03_P5.08mm_Horizont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; MPN Phoenix MKDS 1,5/ 3-5,08 (1715734); LCSC C480520
J5: Qwiic; JST_SH_SM04B-SRSS-TB_1x04-1MP_P1.00mm_Horizontal; MPN JST SM04B-SRSS-TB(LF)(SN); LCSC C160404
J6: AI1-AI6, GND; TerminalBlock_Phoenix_PT-1,5-8-3.5-H_1x08_P3.50mm_Horizontal; MPN Phoenix PT 1,5/ 8-3,5-H (1984675); LCSC C5484501
J7: IO1-IO6, 3V3, GND; TerminalBlock_Phoenix_PT-1,5-8-3.5-H_1x08_P3.50mm_Horizontal; MPN Phoenix PT 1,5/ 8-3,5-H (1984675); LCSC C5484501
J8: 1-Wire; TerminalBlock_Phoenix_PT-1,5-3-3.5-H_1x03_P3.50mm_Horizontal; MPN Phoenix PT 1,5/ 3-3,5-H (1984620); LCSC C3816291
J9: I2C; TerminalBlock_Phoenix_PT-1,5-4-3.5-H_1x04_P3.50mm_Horizontal; MPN Phoenix PT 1,5/ 4-3,5-H (1984633); LCSC C5144867
K1, K2: G2RL-1 DC5; Relay_SPDT_Omron_G2RL-1; MPN Omron G2RL-1 DC5; LCSC C1524672
K3, K4: G3MB-202P DC5; Omron_G3MB-202P_SIP4; MPN Omron G3MB-202P DC5; LCSC C19591980
LED1: green; LED_0603_1608Metric; MPN KENTO KT-0603G; LCSC C12624
LED2, LED3, LED4, LED5: red; LED_0603_1608Metric; MPN KENTO KT-0603R; LCSC C2286
Q1, Q2: MMBT3904; SOT-23; MPN MMBT3904; LCSC C20526
Q3, Q4, Q5, Q6: AO3400A; SOT-23; MPN AOS AO3400A; LCSC C20917
R1, R2: 5.1k 1%; R_0603_1608Metric; MPN Uniroyal 0603WAF5101T5E; LCSC C23186
R3, R19, R20, R21, R22: 1k; R_0603_1608Metric; MPN Uniroyal 0603WAF1001T5E; LCSC C21190
R4, R5, R6, R7: 10k; R_0603_1608Metric; MPN Uniroyal 0603WAF1002T5E; LCSC C25804
R8, R9, R10: 4.7k; R_0603_1608Metric; MPN Uniroyal 0603WAF4701T5E; LCSC C23162
R11, R12, R13, R14, R35, R36, R37, R38, R39, R40: 100; R_0603_1608Metric; MPN Uniroyal 0603WAF1000T5E; LCSC C22775
R15, R16, R17, R18: 100k; R_0603_1608Metric; MPN Uniroyal 0603WAF1003T5E; LCSC C25803
R23, R24, R25, R26, R27, R28: 30k 1%; R_0603_1608Metric; MPN Uniroyal 0603WAF3002T5E; LCSC C22984
R29, R30, R31, R32, R33, R34: 10k 1%; R_0603_1608Metric; MPN Uniroyal 0603WAF1002T5E; LCSC C25804
SW1: RESET; SW_SPST_TL3342; MPN E-Switch TL3342F450QG; LCSC C2886897
SW2: BOOT; SW_SPST_TL3342; MPN E-Switch TL3342F450QG; LCSC C2886897
U1: ESP32-WROOM-32E-N4; ESP32-WROOM-32E; MPN Espressif ESP32-WROOM-32E-N4; LCSC C701341
U2: AP7361C-33E; SOT-223-3_TabPin2; MPN Diodes AP7361C-33E-13; LCSC C500795
U3: CH340C; SOIC-16_3.9x9.9mm_P1.27mm; MPN WCH CH340C; LCSC C84681
U4: USBLC6-2SC6; SOT-23-6; MPN ST USBLC6-2SC6; LCSC C7519
U5, U6: TPD4E05U06; USON-10_2.5x1.0mm_P0.5mm; MPN TI TPD4E05U06DQAR; LCSC C138714

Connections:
3V3_OUT: F2.2, J5.2, J7.7, J8.1, J9.1
+3V3: C4.1, C5.1, C6.1, C8.1, C9.1, C10.1, D6.2 (K), D7.2 (K), D8.2 (K), D9.2 (K), D10.2 (K), D11.2 (K), F2.1, R3.1, R6.2, R7.2, R8.2, R9.2, R10.2, U1.2 (VDD), U2.3 (VO), U3.4 (V3), U3.16 (VCC)
+5V: C1.1, C2.1, C3.1, D1.1 (A1), D4.1 (K), D5.1 (K), F1.2, K1.A1, K2.A1, K3.3, K4.3, LED2.2 (A), LED3.2 (A), LED4.2 (A), LED5.2 (A), U2.1 (VI), U4.5 (VBUS)
AIN1: C11.1, D6.3 (COM), R23.2, R29.1, U1.4 (SENSOR_VP)
AIN2: C12.1, D7.3 (COM), R24.2, R30.1, U1.5 (SENSOR_VN)
AIN3: C13.1, D8.3 (COM), R25.2, R31.1, U1.6 (IO34)
AIN4: C14.1, D9.3 (COM), R26.2, R32.1, U1.7 (IO35)
AIN5: C15.1, D10.3 (COM), R27.2, R33.1, U1.8 (IO32)
AIN6: C16.1, D11.3 (COM), R28.2, R34.1, U1.9 (IO33)
CC1: J1.A5 (CC1), R1.1
CC2: J1.B5 (CC2), R2.1
DQ: D3.1 (A1), J8.2, R10.1, U1.26 (IO4)
DRV1: D4.2 (A), K1.A2, Q3.3 (D), R19.2
DRV2: D5.2 (A), K2.A2, Q4.3 (D), R20.2
DRV3: K3.4, Q5.3 (D), R21.2
DRV4: K4.4, Q6.3 (D), R22.2
DTR: Q2.2 (E), R4.1, U3.13 (~DTR)
EN: C7.1, Q2.3 (C), R6.1, SW1.1, U1.3 (EN)
G1: Q3.1 (G), R11.2, R15.1
G2: Q4.1 (G), R12.2, R16.1
G3: Q5.1 (G), R13.2, R17.1
G4: Q6.1 (G), R14.2, R18.1
GND: C1.2, C2.2, C3.2, C4.2, C5.2, C6.2, C7.2, C8.2, C9.2, C10.2, C11.2, C12.2, C13.2, C14.2, C15.2, C16.2, D1.2 (A2), D3.2 (A2), D6.1 (A), D7.1 (A), D8.1 (A), D9.1 (A), D10.1 (A), D11.1 (A), J1.A1 (GND), J1.A12 (GND), J1.B1 (GND), J1.B12 (GND), J1.SH (SHIELD), J5.1, J6.7, J6.8, J7.8, J8.3, J9.4, LED1.1 (K), Q3.2 (S), Q4.2 (S), Q5.2 (S), Q6.2 (S), R1.2, R2.2, R15.2, R16.2, R17.2, R18.2, R29.2, R30.2, R31.2, R32.2, R33.2, R34.2, SW1.2, SW2.2, U1.1, U1.15, U1.38, U1.39, U1.[1,15,38,39] (GND), U2.2 (GND), U3.1 (GND), U4.2 (GND), U5.3 (GND), U5.8 (GND), U6.3 (GND), U6.8 (GND)
GP1: R35.1, U1.37 (IO23)
GP2: R36.1, U1.10 (IO25)
GP3: R37.1, U1.11 (IO26)
GP4: R38.1, U1.12 (IO27)
GP5: R39.1, U1.16 (IO13)
GP6: R40.1, U1.13 (IO14)
IO0: Q1.3 (C), R7.1, SW2.1, U1.25 (IO0)
LED1_A: LED1.2 (A), R3.2
LED2_K: LED2.1 (K), R19.1
LED3_K: LED3.1 (K), R20.1
LED4_K: LED4.1 (K), R21.1
LED5_K: LED5.1 (K), R22.1
OUT1: R11.1, U1.27 (IO16)
OUT2: R12.1, U1.28 (IO17)
OUT3: R13.1, U1.30 (IO18)
OUT4: R14.1, U1.31 (IO19)
Q1_B: Q1.1 (B), R4.2
Q2_B: Q2.1 (B), R5.2
R1_COM: J2.1, K1.11
R1_NC: J2.3, K1.12
R1_NO: J2.2, K1.14
R2_COM: J3.1, K2.11
R2_NC: J3.3, K2.12
R2_NO: J3.2, K2.14
R3_LF: F3.2, K3.1
R3_LOAD: J4.2, K3.2
R4_LF: F4.2, K4.1
R4_LOAD: J4.3, K4.2
RTS: Q1.2 (E), R5.1, U3.14 (~RTS)
RXD0: U1.34 (RXD0/IO3), U3.2 (TXD)
SCL: J5.4, J9.3, R9.1, U1.36 (IO22), U6.5 (D2-)
SDA: J5.3, J9.2, R8.1, U1.33 (IO21), U6.4 (D2+)
SSR_L: F3.1, F4.1, J4.1
TAI1: J6.1, R23.1
TAI2: J6.2, R24.1
TAI3: J6.3, R25.1
TAI4: J6.4, R26.1
TAI5: J6.5, R27.1
TAI6: J6.6, R28.1
TIO1: J7.1, R35.2, U5.1 (D1+)
TIO2: J7.2, R36.2, U5.2 (D1-)
TIO3: J7.3, R37.2, U5.4 (D2+)
TIO4: J7.4, R38.2, U5.5 (D2-)
TIO5: J7.5, R39.2, U6.1 (D1+)
TIO6: J7.6, R40.2, U6.2 (D1-)
TXD0: U1.35 (TXD0/IO1), U3.3 (RXD)
USB_DM: J1.A7 (D-), J1.B7 (D-), U3.6 (UD-), U4.3 (I/O2), U4.4 (I/O2)
USB_DP: J1.A6 (D+), J1.B6 (D+), U3.5 (UD+), U4.1 (I/O1), U4.6 (I/O1)
VBUS_IN: F1.1, J1.A4 (VBUS), J1.A9 (VBUS), J1.B4 (VBUS), J1.B9 (VBUS)

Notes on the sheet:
Power: USB-C 5 V, 3.3 V regulator
USB-serial (CH340C at 3.3 V) and auto-reset
ESP32-WROOM-32E (never WROVER: GPIO 16/17 are outputs)
Outputs: R1/R2 relays (COM/NO/NC), R3/R4 G3MB-202P SSRs; off at boot
Analog inputs AI1-AI6: 0-10 V, 30k/10k divider (10 V = 2.5 V)
GPIO IO1-IO6 (3.3 V), I2C, 1-Wire

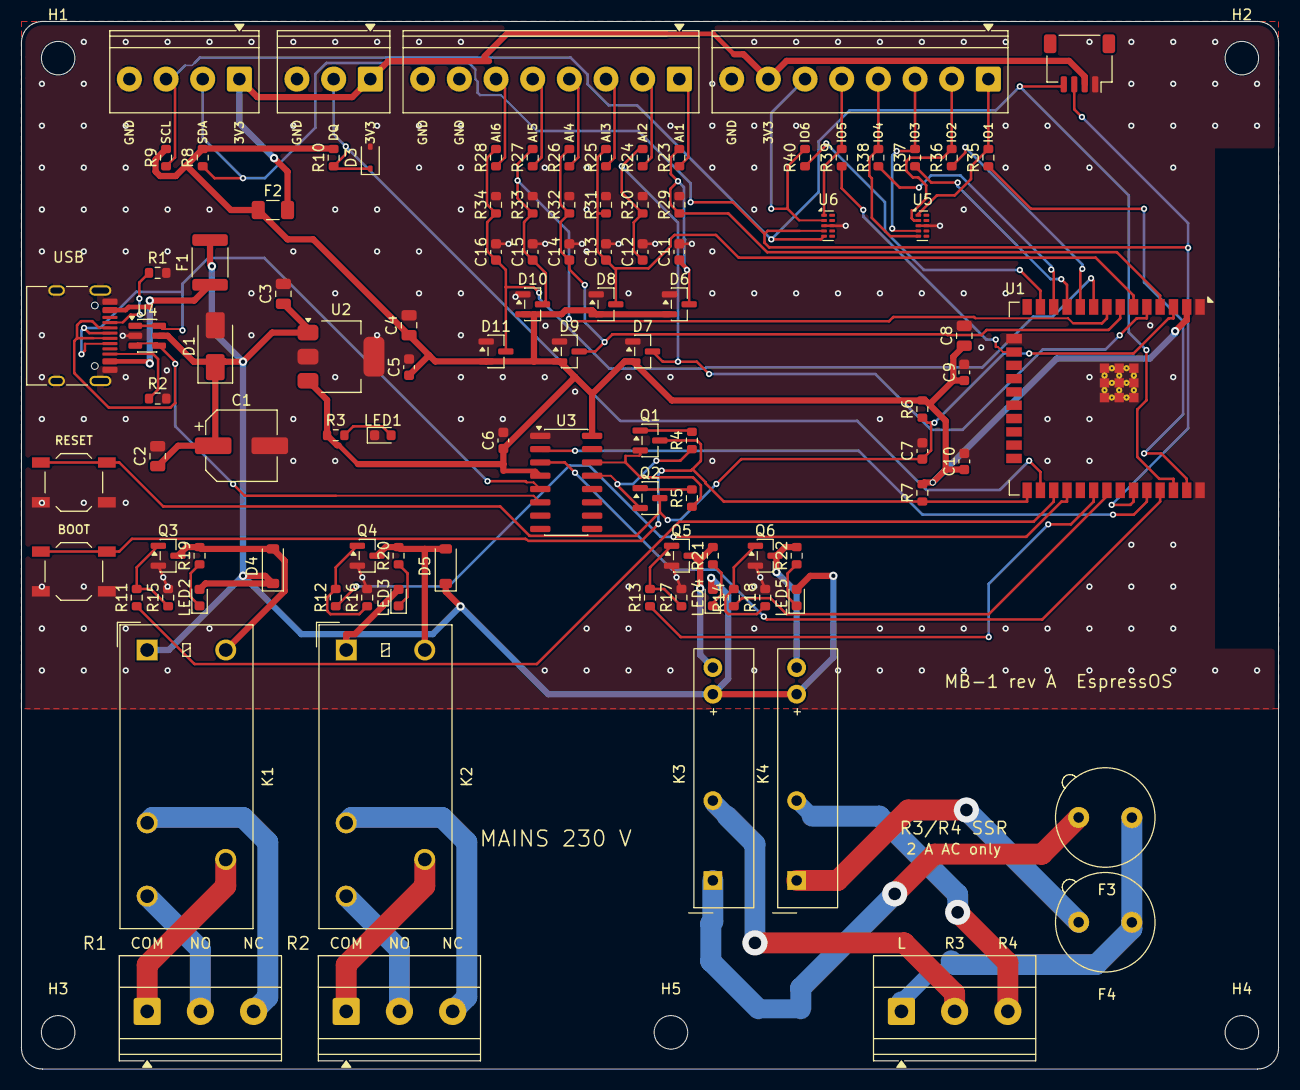
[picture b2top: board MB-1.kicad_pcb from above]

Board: 2 copper layers, 120.0 x 100.0 mm, 107 parts (0 on the bottom side), 72 nets.

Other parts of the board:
H1, H2, H3, H4, H5: MountingHole_3.2mm_M3

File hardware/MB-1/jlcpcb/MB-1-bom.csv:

Comment,Designator,Footprint,LCSC Part #
100u 16V,C1,CP_Elec_6.3x7.7,C2887276
10u,"C2,C3",C_0805_2012Metric,C15850
22u,"C4,C8",C_0805_2012Metric,C45783
100n,"C5,C6,C9,C10,C11,C12,C13,C14,C15,C16",C_0603_1608Metric,C14663
1u,C7,C_0603_1608Metric,C15849
SMAJ5.0A,D1,D_SMA,C83329
PESD3V3L1BA,D3,D_SOD-323,C51450
1N4148W,"D4,D5",D_SOD-123,C81598
BAT54S,"D6,D7,D8,D9,D10,D11",SOT-23,C47546
1.5A hold,F1,Fuse_1812_4532Metric,C89648
0.2A hold,F2,Fuse_1206_3216Metric,C185112
USB-C,J1,USB_C_Receptacle_HRO_TYPE-C-31-M-12,C165948
Qwiic,J5,JST_SH_SM04B-SRSS-TB_1x04-1MP_P1.00mm_Horizontal,C160404
green,LED1,LED_0603_1608Metric,C12624
red,"LED2,LED3,LED4,LED5",LED_0603_1608Metric,C2286
MMBT3904,"Q1,Q2",SOT-23,C20526
AO3400A,"Q3,Q4,Q5,Q6",SOT-23,C20917
5.1k 1%,"R1,R2",R_0603_1608Metric,C23186
1k,"R3,R19,R20,R21,R22",R_0603_1608Metric,C21190
10k,"R4,R5,R6,R7",R_0603_1608Metric,C25804
4.7k,"R8,R9,R10",R_0603_1608Metric,C23162
100,"R11,R12,R13,R14,R35,R36,R37,R38,R39,R40",R_0603_1608Metric,C22775
100k,"R15,R16,R17,R18",R_0603_1608Metric,C25803
30k 1%,"R23,R24,R25,R26,R27,R28",R_0603_1608Metric,C22984
10k 1%,"R29,R30,R31,R32,R33,R34",R_0603_1608Metric,C25804
RESET,SW1,SW_SPST_TL3342,C2886897
BOOT,SW2,SW_SPST_TL3342,C2886897
ESP32-WROOM-32E-N4,U1,ESP32-WROOM-32E,C701341
AP7361C-33E,U2,SOT-223-3_TabPin2,C500795
CH340C,U3,SOIC-16_3.9x9.9mm_P1.27mm,C84681
USBLC6-2SC6,U4,SOT-23-6,C7519
TPD4E05U06,"U5,U6",USON-10_2.5x1.0mm_P0.5mm,C138714

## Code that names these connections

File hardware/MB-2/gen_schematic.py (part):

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part('J2', 'Connector_Generic:Conn_01x15', 'DevKit left', 'SOCK15', {
    # 1 EN, 12 GPIO12 (boot strap): not used
    '2': 'IN1', '3': 'IN2', '4': 'IN3', '5': 'IN4',          # GPIO 36 (VP), 39 (VN), 34, 35
    '6': 'TCH5', '7': 'TCH6', '8': 'GP2', '9': 'GP3',        # GPIO 32, 33, 25, 26
    '10': 'TCH4', '11': 'TCH2', '13': 'TCH1',                # GPIO 27, 14, 13
    '14': 'GND', '15': 'VIN_DK'}, MPN='Female header 1x15, 2.54 mm')
part('J3', 'Connector_Generic:Conn_01x15', 'DevKit right', 'SOCK15', {
    # 3 TX0, 4 RX0, 8 GPIO5, 12 GPIO2: not used
    '1': 'GP1', '2': 'SCL', '5': 'SDA',                      # GPIO 23, 22, 21
    '6': 'OUT4', '7': 'OUT3', '9': 'OUT2', '10': 'OUT1',     # GPIO 19, 18, 17, 16
    '11': 'DQ', '13': 'TCH3', '14': 'GND', '15': '+3V3'},    # GPIO 4, 15
    MPN='Female header 1x15, 2.54 mm')

# Precise analog inputs on an ADS1115 module
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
